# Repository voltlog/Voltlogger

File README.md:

# Voltlogger
This repository contains the source files for the Voltlogger, a 10 channel thermocouple data logger built around the ESP32 and the MAX31855 thermocouple interface chip. This project was shown in Voltlog #368.

## Known bugs in revA
Schematic constains a bug, where IO34 & IO35 are connected to chip select signals for thermocouple interface chips #1 and #2. These pins are input only on the ESP32 so they cannot drive the CS pis on Th1 & Th2. The workaround is to connect these CS pins to IO22 and IO23. ESD protection diodes seem to be causing signal integrity issues on the SD card interface so leave those unpopulated until this issue is debugged further.

More info about this project in [Voltlog #368](https://youtu.be/YB1_f1XHdw0).
If you would like to order one of these boards ready assembled, check out my [Tindie store](https://www.tindie.com/products/voltlog/voltlogger-10-channel-thermocouple-data-logger/).

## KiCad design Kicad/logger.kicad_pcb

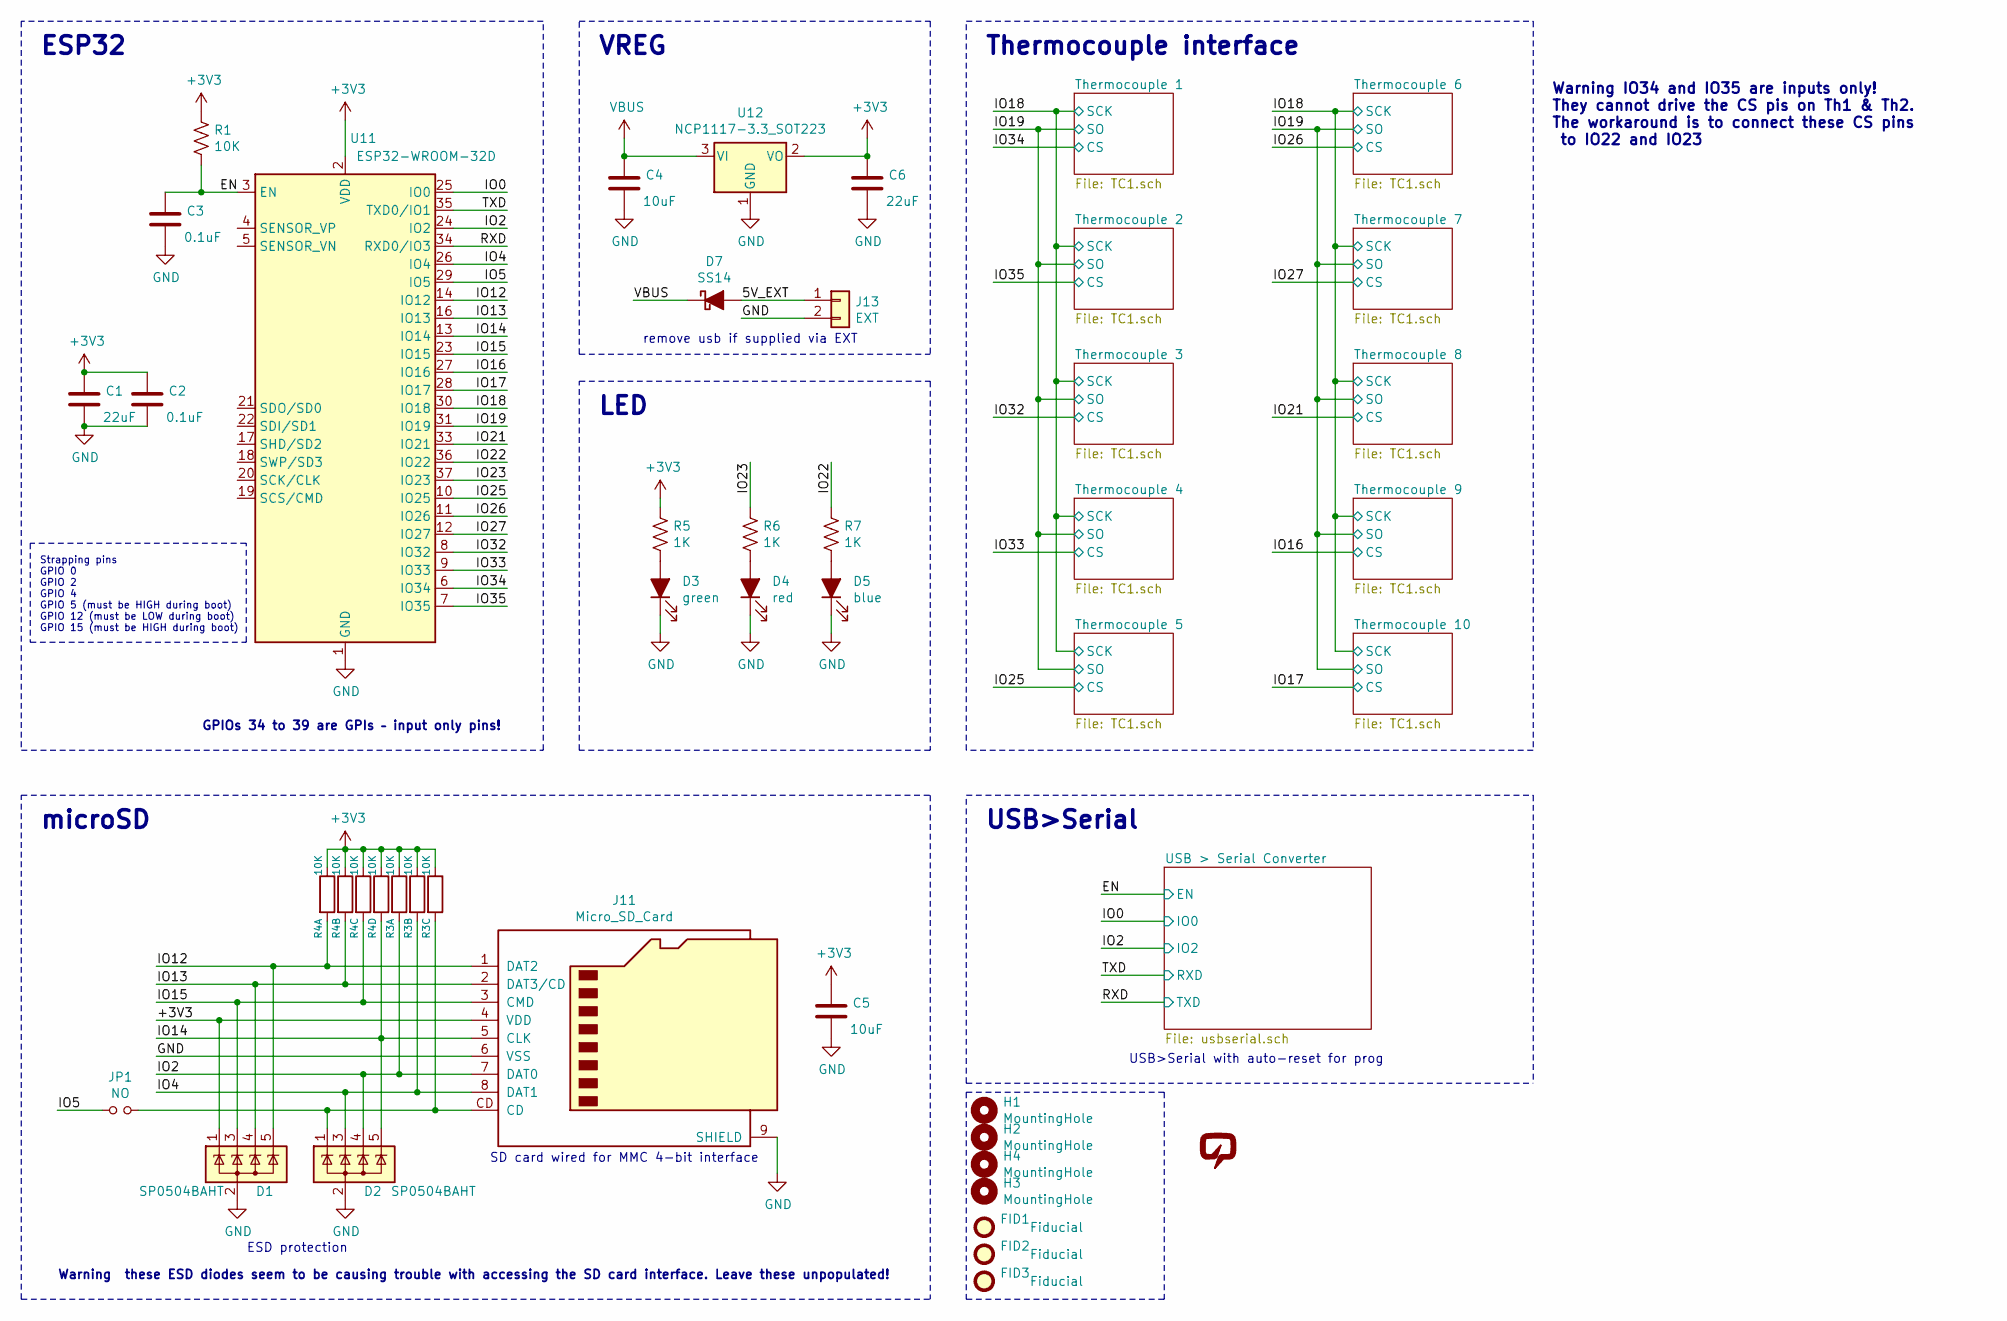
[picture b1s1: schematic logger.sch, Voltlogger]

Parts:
C1, C6: 22uF; C_0805_2012Metric
C2, C3: 0.1uF; C_0603_1608Metric
C4, C5: 10uF; C_0805_2012Metric
D1, D2: SP0504BAHT; SOT-23-5
D3: green; LED_0603_1608Metric
D4: red; LED_0603_1608Metric
D5: blue; LED_0603_1608Metric
D7: SS14; D_SMA
FID1, FID2, FID3: Fiducial; Fiducial_0.75mm_Mask1.5mm
H1, H2, H3, H4: MountingHole; MountingHole_3.2mm_M3_ISO7380_Pad
J11: Micro_SD_Card; XKTF-015-N
J13: EXT; PinHeader_1x02_P2.54mm_Vertical
JP1: NO; SolderJumper-2_P1.3mm_Open_TrianglePad1.0x1.5mm
R1: 10K; R_0603_1608Metric
R3, R4: 10K; R_Array_Convex_4x0603
R5, R6, R7: 1K; R_0603_1608Metric
U11: ESP32-WROOM-32D; ESP32-WROOM-32
U12: NCP1117-3.3_SOT223; SOT-223-3_TabPin2
V1: VOLTLOG_LOGO; voltlog_mask_5mm

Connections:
+3V3: C1.1, C2.1, C5.1, C6.1, D1.1 (K), J11.4 (VDD), R1.1, R3.6, R3.7, R3.8, R4.5, R4.6, R4.7, R4.8, R5.2, U11.2 (VDD), U12.2 (VO); also elsewhere on the board
/5V_EXT: D7.2 (A), J13.1
/EN: C3.1, R1.2, U11.3 (EN); also elsewhere on the board
/IO0: U11.25 (IO0); also elsewhere on the board
/IO2: D2.4 (K), J11.7 (DAT0), R3.1, U11.24 (IO2); also elsewhere on the board
/IO4: D2.3 (K), J11.8 (DAT1), R3.2, U11.26 (IO4)
/IO5: JP1.2, U11.29 (IO5)
/IO12: D1.5 (K), J11.1 (DAT2), R4.1, U11.14 (IO12)
/IO13: D1.4 (K), J11.2 (DAT3/CD), R4.2, U11.16 (IO13)
/IO14: D2.5 (K), J11.5 (CLK), R4.4, U11.13 (IO14)
/IO15: D1.3 (K), J11.3 (CMD), R4.3, U11.23 (IO15)
/IO16: U11.27 (IO16); also elsewhere on the board
/IO17: U11.28 (IO17); also elsewhere on the board
/IO18: U11.30 (IO18); also elsewhere on the board
/IO19: U11.31 (IO19); also elsewhere on the board
/IO21: U11.33 (IO21); also elsewhere on the board
/IO22: R7.2, U11.36 (IO22)
/IO23: R6.2, U11.37 (IO23)
/IO25: U11.10 (IO25); also elsewhere on the board
/IO26: U11.11 (IO26); also elsewhere on the board
/IO27: U11.12 (IO27); also elsewhere on the board
/IO32: U11.8 (IO32); also elsewhere on the board
/IO33: U11.9 (IO33); also elsewhere on the board
/IO34: U11.6 (IO34); also elsewhere on the board
/IO35: U11.7 (IO35); also elsewhere on the board
/RXD: U11.34 (RXD0/IO3); also elsewhere on the board
/TXD: U11.35 (TXD0/IO1); also elsewhere on the board
GND: C1.2, C2.2, C3.2, C4.2, C5.2, C6.2, D1.2 (A), D2.2 (A), D3.1 (K), D4.1 (K), D5.1 (K), J11.6 (VSS), J11.9 (SHIELD), J13.2, U11.1 (GND), U11.15 (GND), U11.38 (GND), U11.39 (GND), U12.1 (GND); also elsewhere on the board
unnamed: D2.1 (K), J11.CD, JP1.1, R3.3
unnamed: D3.2 (A), R5.1
unnamed: D4.2 (A), R6.1
unnamed: D5.2 (A), R7.1
VBUS: C4.1, D7.1 (K), U12.3 (VI); also elsewhere on the board

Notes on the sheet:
SD card wired for MMC 4-bit interface
Strapping pins GPIO 0 GPIO 2 GPIO 4 GPIO 5 (must be HIGH during boot) GPIO 12 (must be LOW during boot) GPIO 15 (must be HIGH during boot)
ESP32
VREG
remove usb if supplied via EXT
LED
microSD
ESD protection
Thermocouple interface
USB>Serial
USB>Serial with auto-reset for prog
GPIOs 34 to 39 are GPIs – input only pins!
Warning IO34 and IO35 are inputs only! They cannot drive the CS pis on Th1 & Th2. The workaround is to connect these CS pins to IO22 and IO23
Warning these ESD diodes seem to be causing trouble with accessing the SD card interface. Leave these unpopulated!

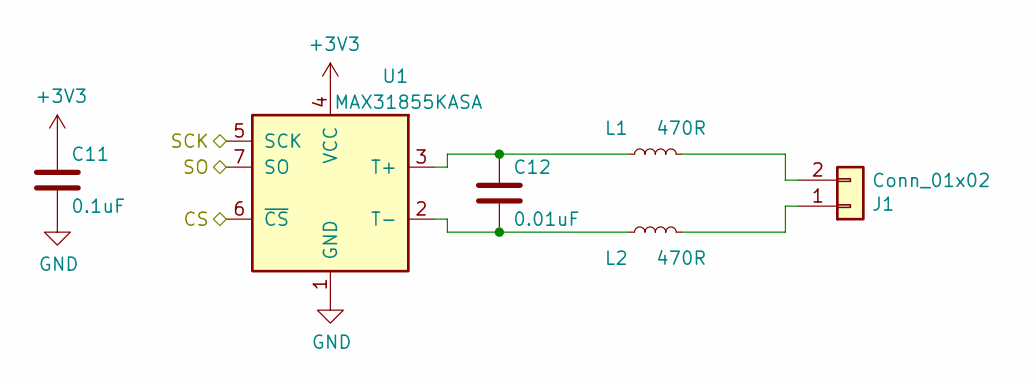
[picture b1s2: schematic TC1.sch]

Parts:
C11: 0.1uF; C_0603_1608Metric
C12: 0.01uF; C_0603_1608Metric
J1: Conn_01x02; TerminalBlock_MetzConnect_Type094_RT03502HBLU_1x02_P5.00mm_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
L1, L2: 470R; L_0603_1608Metric
U1: MAX31855KASA; SOIC-8_3.9x4.9mm_P1.27mm

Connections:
+3V3: C11.1, U1.4 (VCC); also elsewhere on the board
/IO18: U1.5 (SCK); also elsewhere on the board
/IO19: U1.7 (SO); also elsewhere on the board
/IO34: U1.6 (~CS~); also elsewhere on the board
GND: C11.2, U1.1 (GND); also elsewhere on the board
unnamed: C12.1, L1.1, U1.3 (T+)
unnamed: C12.2, L2.1, U1.2 (T-)
unnamed: J1.1, L2.2
unnamed: J1.2, L1.2

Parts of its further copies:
C13, C15, C17, C19, C21, C23, C25, C27, C29: 0.1uF; C_0603_1608Metric
C14, C16, C18, C20, C22, C24, C26, C28, C30: 0.01uF; C_0603_1608Metric
J2, J3, J4, J5, J6, J7, J8, J9, J10: Conn_01x02; TerminalBlock_MetzConnect_Type094_RT03502HBLU_1x02_P5.00mm_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
L3, L4, L5, L6, L7, L8, L9, L10, L11, L12, L13, L14, L15, L16, L17, L18, L19, L20: 470R; L_0603_1608Metric
U2, U3, U4, U5, U6, U7, U8, U9, U10: MAX31855KASA; SOIC-8_3.9x4.9mm_P1.27mm

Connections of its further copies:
+3V3: C13.1, C15.1, C17.1, C19.1, C21.1, C23.1, C25.1, C27.1, C29.1, U2.4 (VCC), U3.4 (VCC), U4.4 (VCC), U5.4 (VCC), U6.4 (VCC), U7.4 (VCC), U8.4 (VCC), U9.4 (VCC), U10.4 (VCC); also elsewhere on the board
/IO16: U9.6 (~CS~); also elsewhere on the board
/IO17: U10.6 (~CS~); also elsewhere on the board
/IO18: U2.5 (SCK), U3.5 (SCK), U4.5 (SCK), U5.5 (SCK), U6.5 (SCK), U7.5 (SCK), U8.5 (SCK), U9.5 (SCK), U10.5 (SCK); also elsewhere on the board
/IO19: U2.7 (SO), U3.7 (SO), U4.7 (SO), U5.7 (SO), U6.7 (SO), U7.7 (SO), U8.7 (SO), U9.7 (SO), U10.7 (SO); also elsewhere on the board
/IO21: U8.6 (~CS~); also elsewhere on the board
/IO25: U5.6 (~CS~); also elsewhere on the board
/IO26: U6.6 (~CS~); also elsewhere on the board
/IO27: U7.6 (~CS~); also elsewhere on the board
/IO32: U3.6 (~CS~); also elsewhere on the board
/IO33: U4.6 (~CS~); also elsewhere on the board
/IO35: U2.6 (~CS~); also elsewhere on the board
GND: C13.2, C15.2, C17.2, C19.2, C21.2, C23.2, C25.2, C27.2, C29.2, U2.1 (GND), U3.1 (GND), U4.1 (GND), U5.1 (GND), U6.1 (GND), U7.1 (GND), U8.1 (GND), U9.1 (GND), U10.1 (GND); also elsewhere on the board
unnamed: C14.1, L3.1, U2.3 (T+)
unnamed: C14.2, L4.1, U2.2 (T-)
unnamed: C16.1, L5.1, U3.3 (T+)
unnamed: C16.2, L6.1, U3.2 (T-)
unnamed: C18.1, L7.1, U4.3 (T+)
unnamed: C18.2, L8.1, U4.2 (T-)
unnamed: C20.1, L9.1, U5.3 (T+)
unnamed: C20.2, L10.1, U5.2 (T-)
unnamed: C22.1, L11.1, U6.3 (T+)
unnamed: C22.2, L12.1, U6.2 (T-)
unnamed: C24.1, L13.1, U7.3 (T+)
unnamed: C24.2, L14.1, U7.2 (T-)
unnamed: C26.1, L15.1, U8.3 (T+)
unnamed: C26.2, L16.1, U8.2 (T-)
unnamed: C28.1, L17.1, U9.3 (T+)
unnamed: C28.2, L18.1, U9.2 (T-)
unnamed: C30.1, L19.1, U10.3 (T+)
unnamed: C30.2, L20.1, U10.2 (T-)
unnamed: J2.1, L4.2
unnamed: J2.2, L3.2
unnamed: J3.1, L6.2
unnamed: J3.2, L5.2
unnamed: J4.1, L8.2
unnamed: J4.2, L7.2
unnamed: J5.1, L10.2
unnamed: J5.2, L9.2
unnamed: J6.1, L12.2
unnamed: J6.2, L11.2
unnamed: J7.1, L14.2
unnamed: J7.2, L13.2
unnamed: J8.1, L16.2
unnamed: J8.2, L15.2
unnamed: J9.1, L18.2
unnamed: J9.2, L17.2
unnamed: J10.1, L20.2
unnamed: J10.2, L19.2

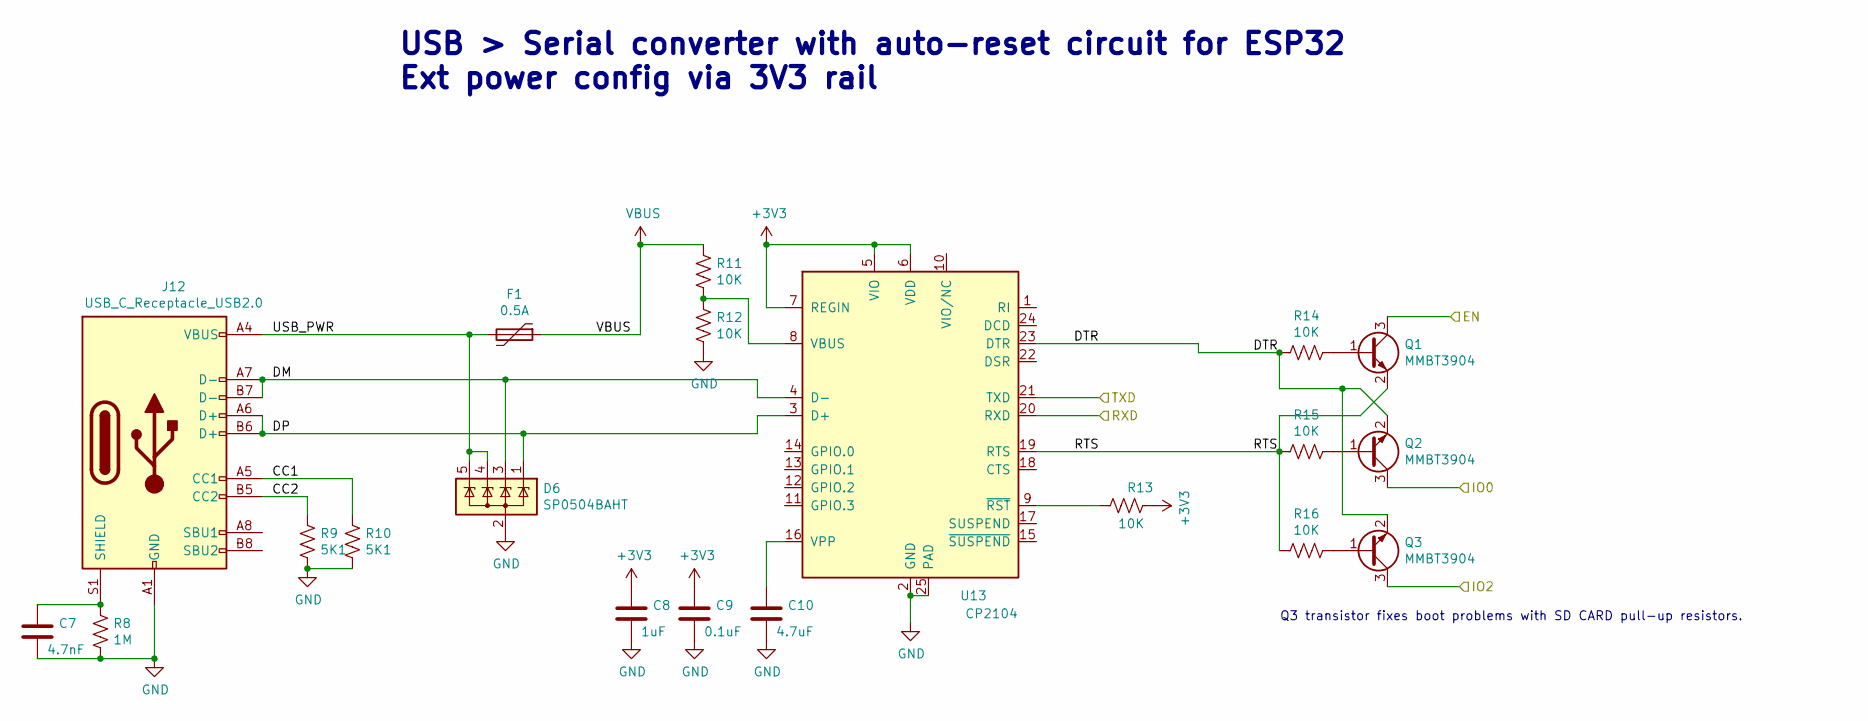
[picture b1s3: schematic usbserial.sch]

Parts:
C7: 4.7nF; C_0603_1608Metric
C8: 1uF; C_0603_1608Metric
C9: 0.1uF; C_0603_1608Metric
C10: 4.7uF; C_0603_1608Metric
D6: SP0504BAHT; SOT-23-5
F1: 0.5A; Fuse_0805_2012Metric
J12: USB_C_Receptacle_USB2.0; TYPE-C-31-M-12
Q1, Q2, Q3: MMBT3904; SOT-23
R8: 1M; R_0603_1608Metric
R9, R10: 5K1; R_0603_1608Metric
R11, R12, R13, R14, R15, R16: 10K; R_0603_1608Metric
U13: CP2104; QFN-24-1EP_4x4mm_P0.5mm_EP2.6x2.6mm

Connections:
+3V3: C8.1, C9.1, R13.2, U13.5 (VIO), U13.6 (VDD), U13.7 (REGIN); also elsewhere on the board
/EN: Q1.3 (C); also elsewhere on the board
/IO0: Q2.3 (C); also elsewhere on the board
/IO2: Q3.3 (C); also elsewhere on the board
/RXD: U13.21 (TXD); also elsewhere on the board
/TXD: U13.20 (RXD); also elsewhere on the board
/USB > Serial Converter/CC1: J12.A5 (CC1), R10.1
/USB > Serial Converter/CC2: J12.B5 (CC2), R9.1
/USB > Serial Converter/DM: D6.3 (K), J12.A7 (D-), J12.B7 (D-), U13.4 (D-)
/USB > Serial Converter/DP: D6.1 (K), J12.A6 (D+), J12.B6 (D+), U13.3 (D+)
/USB > Serial Converter/DTR: Q2.2 (E), Q3.2 (E), R14.2, U13.23 (DTR)
/USB > Serial Converter/RTS: Q1.2 (E), R15.2, R16.2, U13.19 (RTS)
/USB > Serial Converter/USB_PWR: D6.4 (K), D6.5 (K), F1.2, J12.A4 (VBUS), J12.A9 (VBUS), J12.B4 (VBUS), J12.B9 (VBUS)
GND: C7.2, C8.2, C9.2, C10.2, D6.2 (A), J12.A1 (GND), J12.A12 (GND), J12.B1 (GND), J12.B12 (GND), R8.2, R9.2, R10.2, R12.1, U13.2 (GND), U13.25 (PAD); also elsewhere on the board
unnamed: C7.1, J12.S1 (SHIELD), R8.1
unnamed: C10.1, U13.16 (VPP)
unnamed: Q1.1 (B), R14.1
unnamed: Q2.1 (B), R15.1
unnamed: Q3.1 (B), R16.1
unnamed: R11.1, R12.2, U13.8 (VBUS)
unnamed: R13.1, U13.9 (~RST)
VBUS: F1.1, R11.2; also elsewhere on the board

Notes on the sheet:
USB > Serial converter with auto-reset circuit for ESP32 Ext power config via 3V3 rail
Q3 transistor fixes boot problems with SD CARD pull-up resistors.

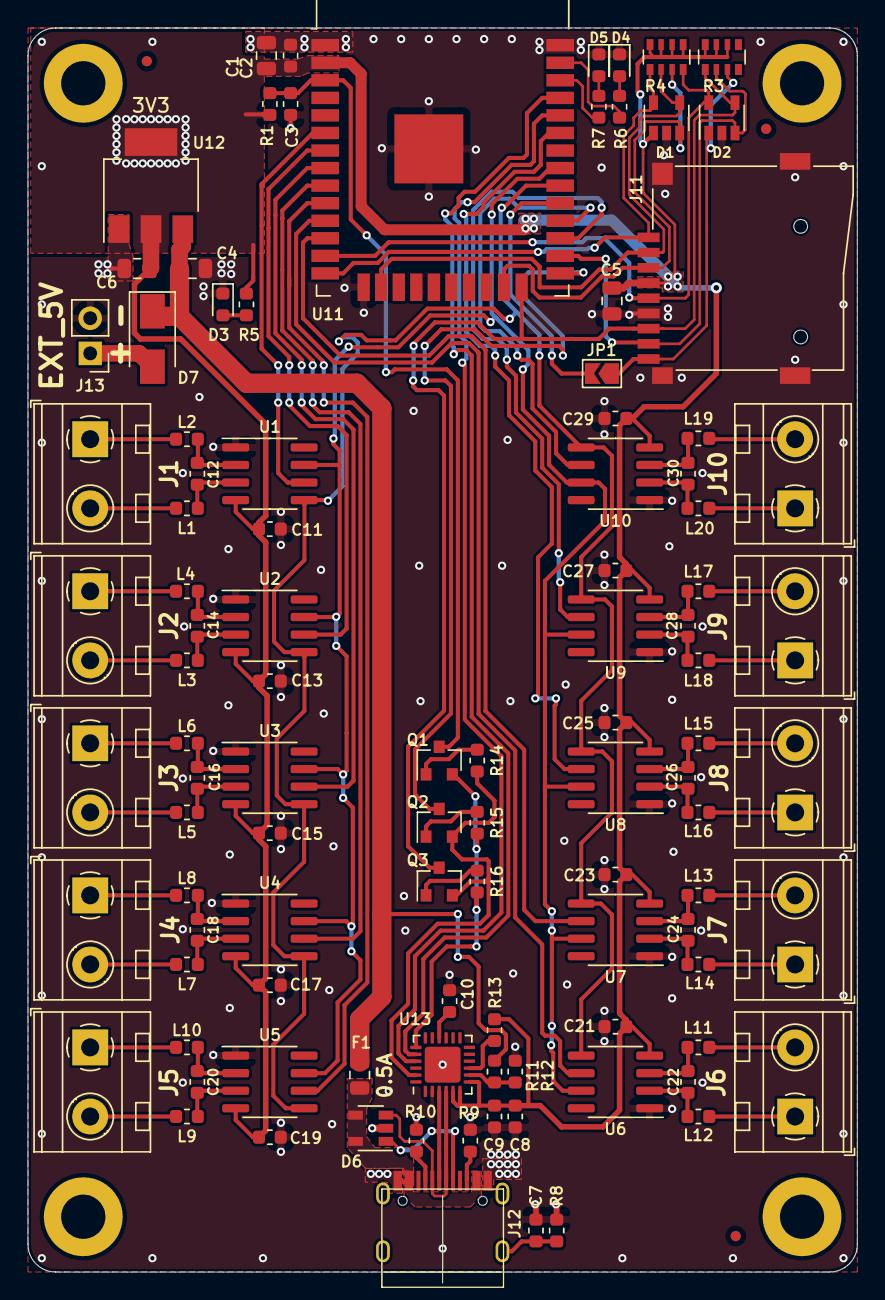
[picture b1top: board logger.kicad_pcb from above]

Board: 2 copper layers, 60.0 x 90.0 mm, 111 parts (0 on the bottom side), 87 nets.

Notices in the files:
Kicad/logger.sch:
Copyright Voltlog License GPLv3
